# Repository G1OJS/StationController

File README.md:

Simple bespoke station controller specific to my needs

Controls antenna relays, magloop tuner and talks to IC7100 and WSJT-x

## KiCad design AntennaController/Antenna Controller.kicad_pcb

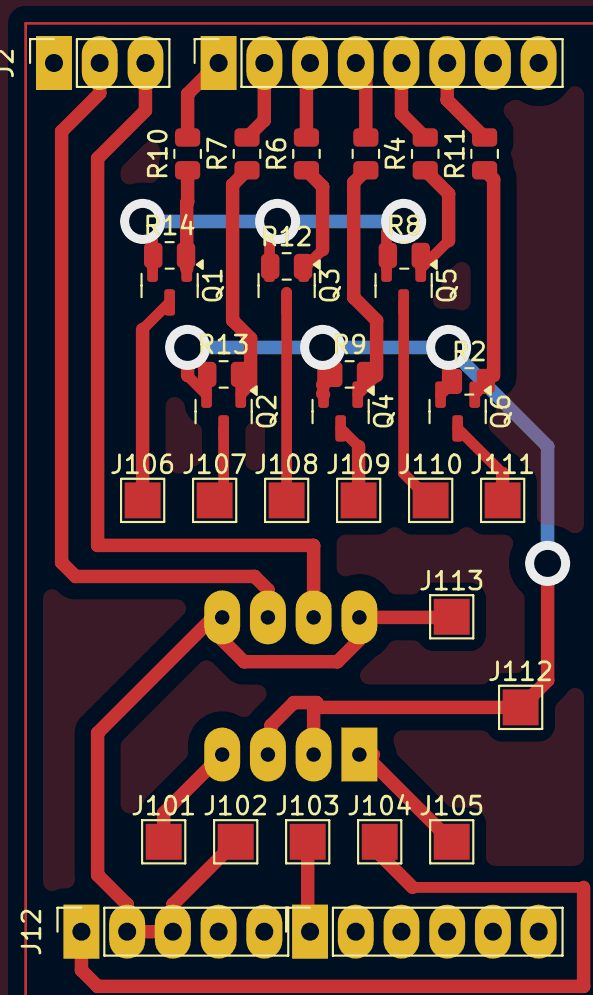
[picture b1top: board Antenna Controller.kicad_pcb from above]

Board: 2 copper layers, 36 parts (1 on the bottom side), 24 nets.

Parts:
J2: Conn_01x03; PinSocket_1x03_P2.54mm_Vertical
J3: Analog; PinSocket_1x06_P2.54mm_Vertical
J4: Digital/PWM; PinSocket_1x08_P2.54mm_Vertical
J12: Conn_01x05; PinSocket_1x05_P2.54mm_Vertical
J101, J102, J103, J104, J105, J106, J107, J108, J109, J110, J111, J112, J113: TestPoint_Pad_2.0x2.0mm
Q1, Q2, Q3, Q4, Q5, Q6: MMBT3906; SOT-23
R2, R8, R9, R12, R13, R14: 270R; R_0805_2012Metric
R4, R5, R6, R7, R10, R11: 3k9; R_0805_2012Metric
U1: L9110H; DIP-8_W7.62mm

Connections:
/2: J4.6, R11.2
/4: J4.4, R5.2
/5V: J12.1, J104.1
/7: J4.1, R10.2
/8: J2.3, U1.7 (In_B)
/9: J2.2, U1.6 (In_A)
/*3: J4.5, R4.2
/*5: J4.3, R6.2
/*6: J4.2, R7.2
/A0: J3.1, J103.1
GND: J12.2, J12.3, J102.1, J113.1, U1.5 (GND), U1.8 (GND)
unnamed: Q1.1 (B), R10.1, R14.2
unnamed: J106.1, Q1.3 (C)
unnamed: Q1.2 (E), Q2.2 (E), Q3.2 (E), Q4.2 (E), Q5.2 (E), Q6.2 (E), R2.1, R8.1, R9.1, R12.1, R13.1, R14.1, U1.2 (Vcc), U1.3 (Vcc)
unnamed: Q2.1 (B), R7.1, R13.2
unnamed: J107.1, Q2.3 (C)
unnamed: Q3.1 (B), R6.1, R12.2
unnamed: J108.1, Q3.3 (C)
unnamed: Q4.1 (B), R5.1, R9.2
unnamed: J109.1, Q4.3 (C)
unnamed: Q5.1 (B), R4.1, R8.2
unnamed: J110.1, Q5.3 (C)
unnamed: Q6.1 (B), R2.2, R11.1
unnamed: J111.1, Q6.3 (C)

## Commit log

2025-09-24 Upload
2025-09-24 initial
2025-09-25 Both comms working but not threaded
2025-09-25 wsjt as a class in develpment
2025-09-26 Auto-detects WSJTX and connects
2025-09-26 prevent crash with radio off
2025-09-26 Improved handshaking
2025-09-26 Detecting PTT commands
2025-09-26 ptt cmds
2025-09-26 PTT connection working
2025-09-27 Better top level structure
2025-09-27 Robust to closing and reopening WSJT-x
2025-10-26 fix loss of audio on wsjt-x
2025-11-06 Add image to README for visual reference
